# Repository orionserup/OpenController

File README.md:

# OpenController
An Open Source Remote Controller utilizing BLE as a Communication Protocol

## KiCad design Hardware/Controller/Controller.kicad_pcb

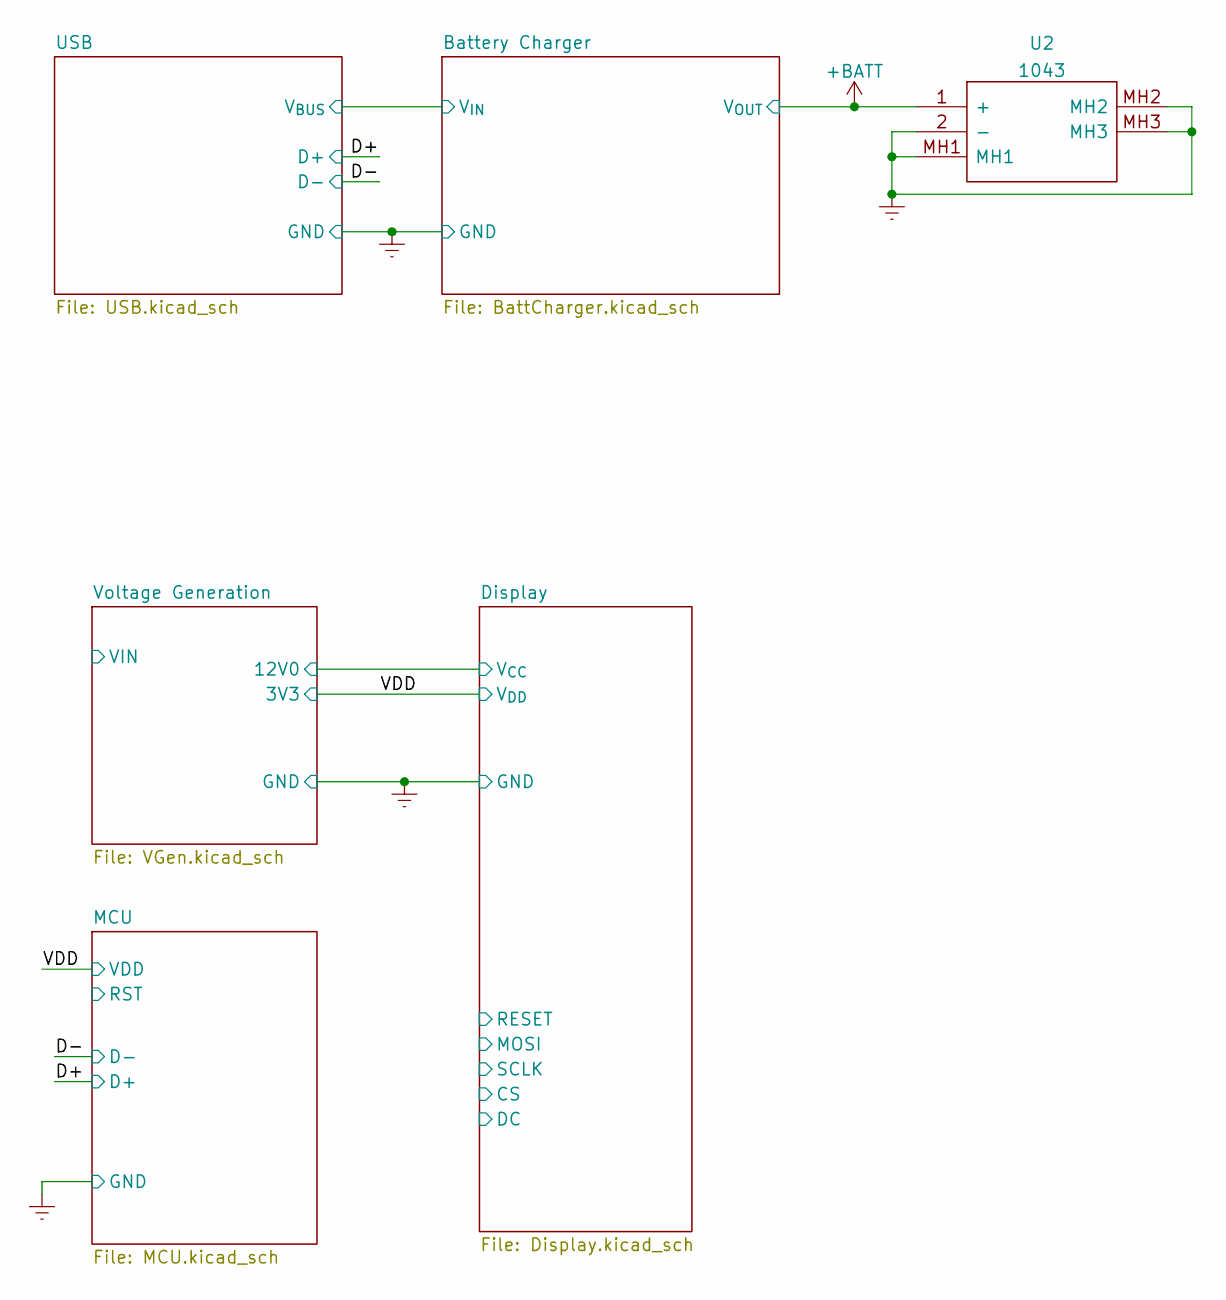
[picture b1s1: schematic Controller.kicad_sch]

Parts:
U2: 1043; Mouser Part Number 534-1043

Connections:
+BATT: U2.1 (+); also elsewhere on the board
Earth: U2.2 (-), U2.MH1, U2.MH2, U2.MH3; also elsewhere on the board

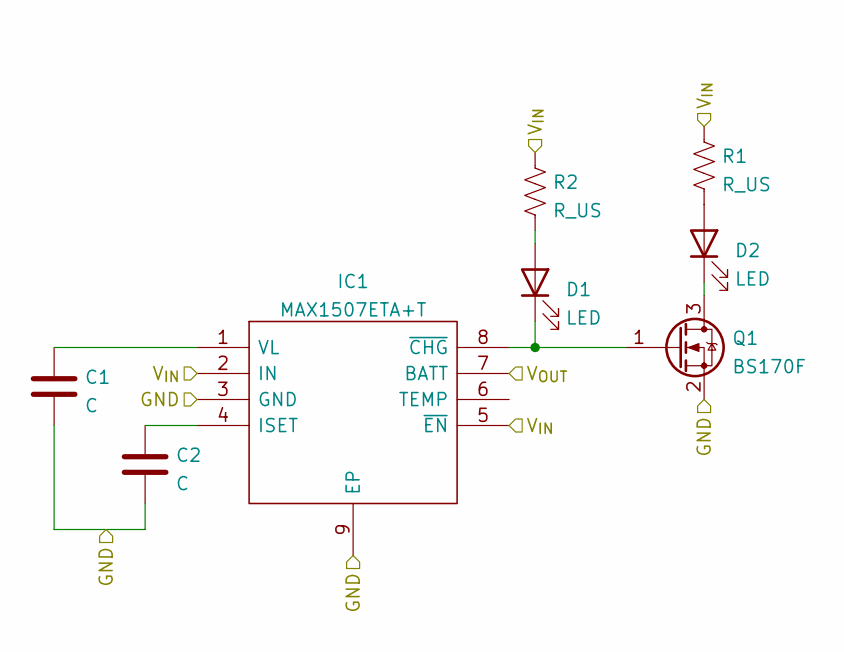
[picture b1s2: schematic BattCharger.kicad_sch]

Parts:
C1, C2: C; C_0603_1608Metric
D1, D2: LED; LED_0603_1608Metric
IC1: MAX1507ETA+T; SON65P300X300X80-9N; Mouser Part Number 700-MAX1507ETA+T
Q1: BS170F; SOT-23
R1, R2: R_US; R_0603_1608Metric

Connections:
+BATT: IC1.7 (BATT); also elsewhere on the board
/Battery Charger/V_{IN}: IC1.2 (IN), IC1.5 (~EN), R1.1, R2.1; also elsewhere on the board
Earth: C1.2, C2.2, IC1.3 (GND), IC1.9 (EP), Q1.2 (S); also elsewhere on the board
unnamed: C2.1, IC1.4 (ISET)
unnamed: D1.1 (K), IC1.8 (~CHG), Q1.1 (G)
unnamed: D1.2 (A), R2.2
unnamed: D2.1 (K), Q1.3 (D)
unnamed: C1.1, IC1.1 (VL)
unnamed: D2.2 (A), R1.2

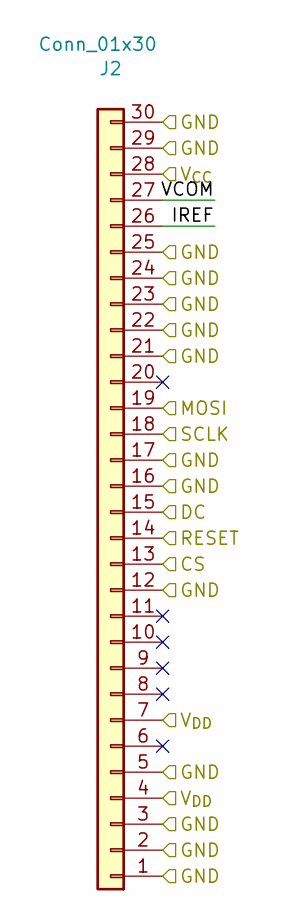
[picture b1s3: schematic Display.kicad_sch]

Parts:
J2: Conn_01x30

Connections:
unnamed: J2.1, J2.2, J2.3, J2.5, J2.12, J2.16, J2.17, J2.21, J2.22, J2.23, J2.24, J2.25, J2.29, J2.30
unnamed: J2.4, J2.7

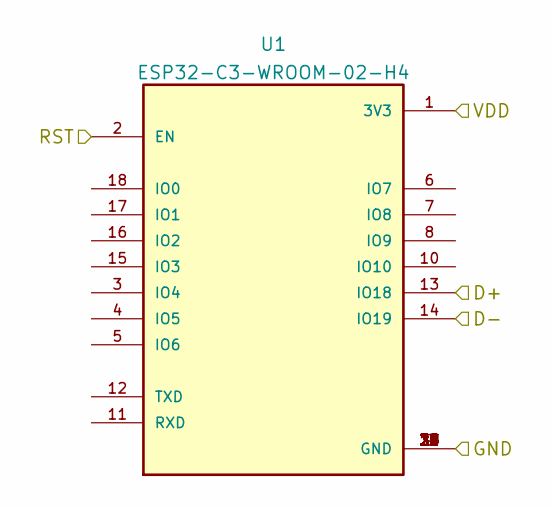
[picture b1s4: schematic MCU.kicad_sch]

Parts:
U1: ESP32-C3-WROOM-02-H4; MODULE_ESP32-C3-WROOM-02-H4; PARTREV V1.0

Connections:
/D+: U1.13 (IO18); also elsewhere on the board
/D-: U1.14 (IO19); also elsewhere on the board
/MCU/RST: U1.2 (EN)
/VDD: U1.1 (3V3); also elsewhere on the board
Earth: U1.9 (GND), U1.19 (GND), U1.20 (GND), U1.21 (GND), U1.22 (GND), U1.23 (GND), U1.24 (GND), U1.25 (GND), U1.26 (GND), U1.27 (GND), U1.28 (GND), U1.29 (GND), U1.30 (GND), U1.31 (GND), U1.32 (GND), U1.33 (GND), U1.34 (GND), U1.35 (GND), U1.36 (GND), U1.37 (GND), U1.38 (GND), U1.39 (GND); also elsewhere on the board

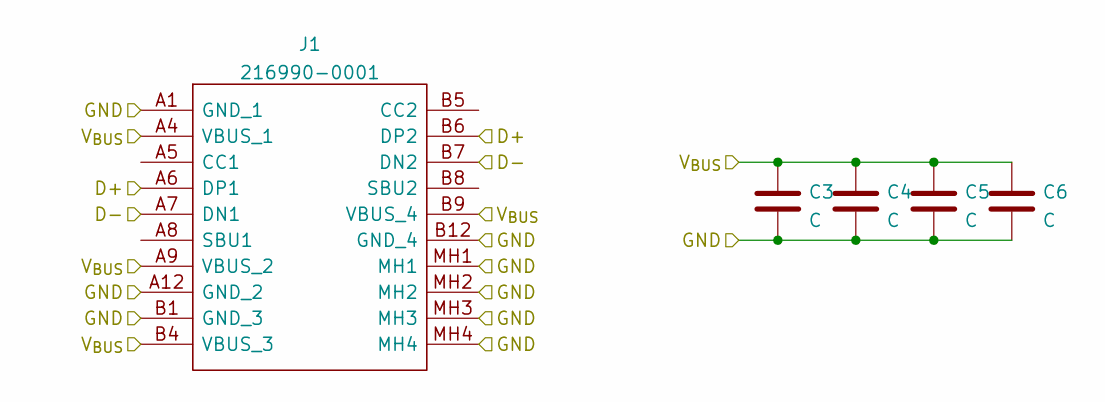
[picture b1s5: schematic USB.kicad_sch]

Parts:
C3, C4, C5, C6: C; C_0603_1608Metric
J1: 216990-0001; 2169900001; Mouser Part Number 538-216990-0001

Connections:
/Battery Charger/V_{IN}: C3.1, C4.1, C5.1, C6.1, J1.A4 (VBUS_1), J1.A9 (VBUS_2), J1.B4 (VBUS_3), J1.B9 (VBUS_4); also elsewhere on the board
/D+: J1.A6 (DP1), J1.B6 (DP2); also elsewhere on the board
/D-: J1.A7 (DN1), J1.B7 (DN2); also elsewhere on the board
Earth: C3.2, C4.2, C5.2, C6.2, J1.A1 (GND_1), J1.A12 (GND_2), J1.B1 (GND_3), J1.B12 (GND_4), J1.MH1, J1.MH2, J1.MH3, J1.MH4; also elsewhere on the board

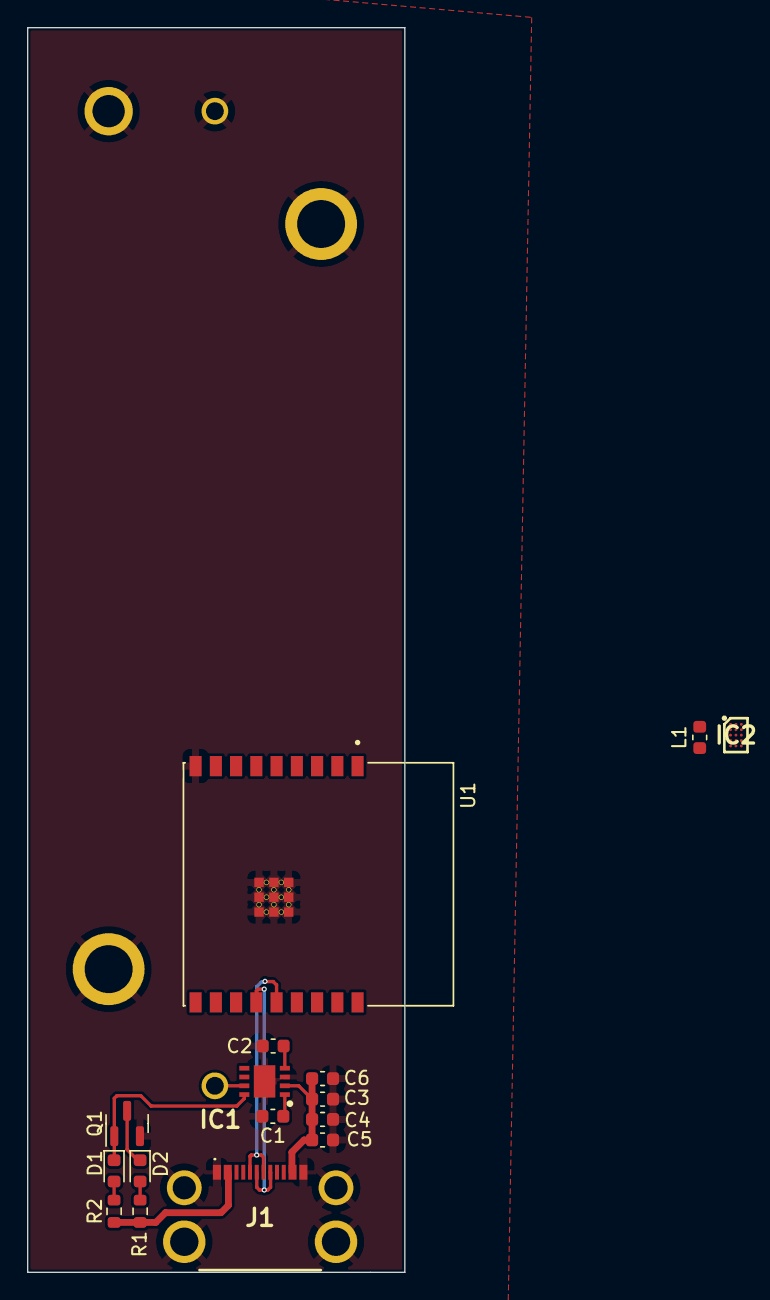
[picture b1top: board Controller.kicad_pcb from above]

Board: 2 copper layers, 27.9 x 92.2 mm, 17 parts (1 on the bottom side), 15 nets.

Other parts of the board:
IC2: ISL91107IIAZ-T7A; BGA15C40P3X5_151X215X55
L1: L; L_0603_1608Metric

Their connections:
/VDD: IC2.E1 (VOUT_1), IC2.E2 (VOUT_2); also elsewhere on the board
/Voltage Generation/LX1: IC2.B1 (LX1_1), IC2.B2 (LX1_2), L1.1
/Voltage Generation/LX2: IC2.D1 (LX2_1), IC2.D2 (LX2_2), L1.2
/Voltage Generation/VIN: IC2.A1 (PVIN_1), IC2.A2 (PVIN_2), IC2.A3 (VIN), IC2.B3 (EN), IC2.C3 (MODE)
Earth: IC2.C1 (PGND_1), IC2.C2 (PGND_2), IC2.D3 (GND); also elsewhere on the board

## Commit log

2022-03-02 structure
